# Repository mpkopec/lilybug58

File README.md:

# lilybug58

**Work in progress.** lilybug58 is a split keyboard derived from
[Bug54](https://github.com/ogruendel/bug54-zmk-config) by ogruendel, and this
repository is a fork of the Bug54 repository. It keeps Bug54's
compact, column-staggered layout and adds two keys per half taken from
[Lily58](https://github.com/kata0510/Lily58), for 58 keys in total:

- an index-finger key beside the innermost column, centred between its two
  lowest keys, in the position of the Lily58 extra key;
- a fifth key below the ring-finger column, where a Super key typically sits.

## Status

The design is at an early stage, and nothing in this repository has been
manufactured or tested yet. The PCB is being redesigned in KiCad, starting
from Bug54's ergogen-generated boards, and the firmware moves from ZMK to
QMK.

## Design

- **PCB:** KiCad 10, one project per half in `kicad/`.
- **Microcontroller:** Adafruit Feather RP2040 in the first revision. A later
  revision is planned to stack footprints for several controller boards, so
  that builders can use the board they already own.
- **Firmware:** QMK.
- **Layout sandbox:** ergogen, in `ergogen/`, used to try key positions and
  outlines. `npm install && npm run generate` writes its output to
  `ergogen/output/`; the KiCad projects remain the master copy of the PCB.
- **Case:** `mech/Case.FCStd` is Bug54's FreeCAD case, kept as the starting
  point for the lilybug58 case.

## Credits and license

Based on Bug54 by ogruendel, with key positions taken from Lily58 by
kata0510. Licensed under CC BY 4.0, as inherited from Bug54; see `LICENSE`.

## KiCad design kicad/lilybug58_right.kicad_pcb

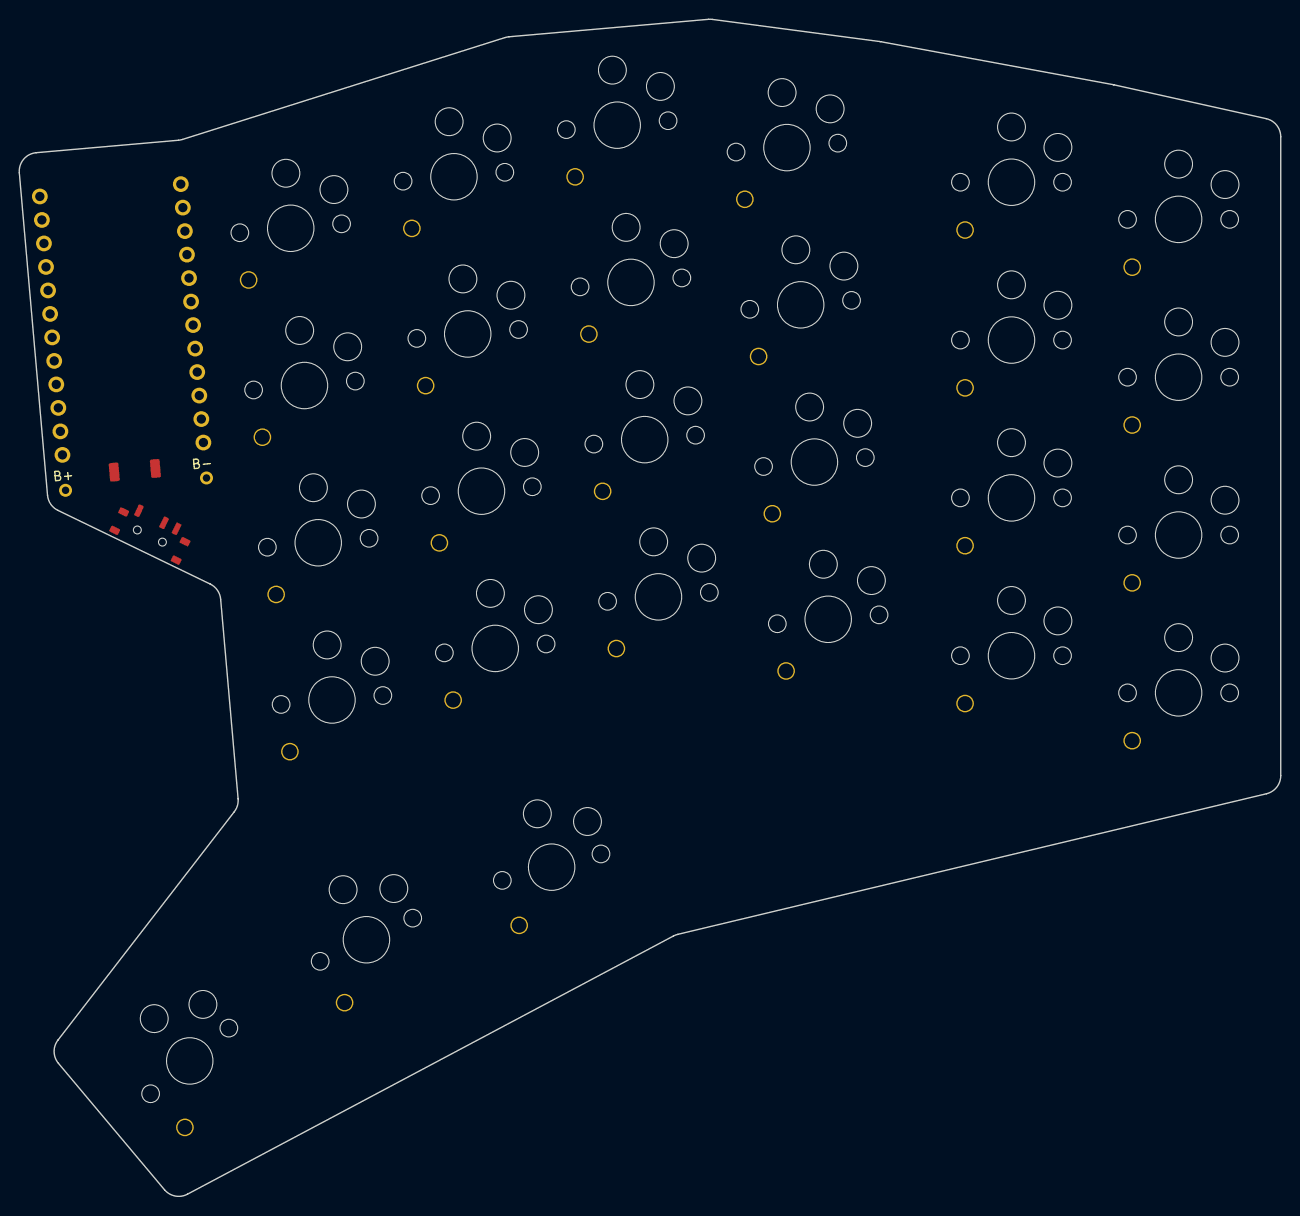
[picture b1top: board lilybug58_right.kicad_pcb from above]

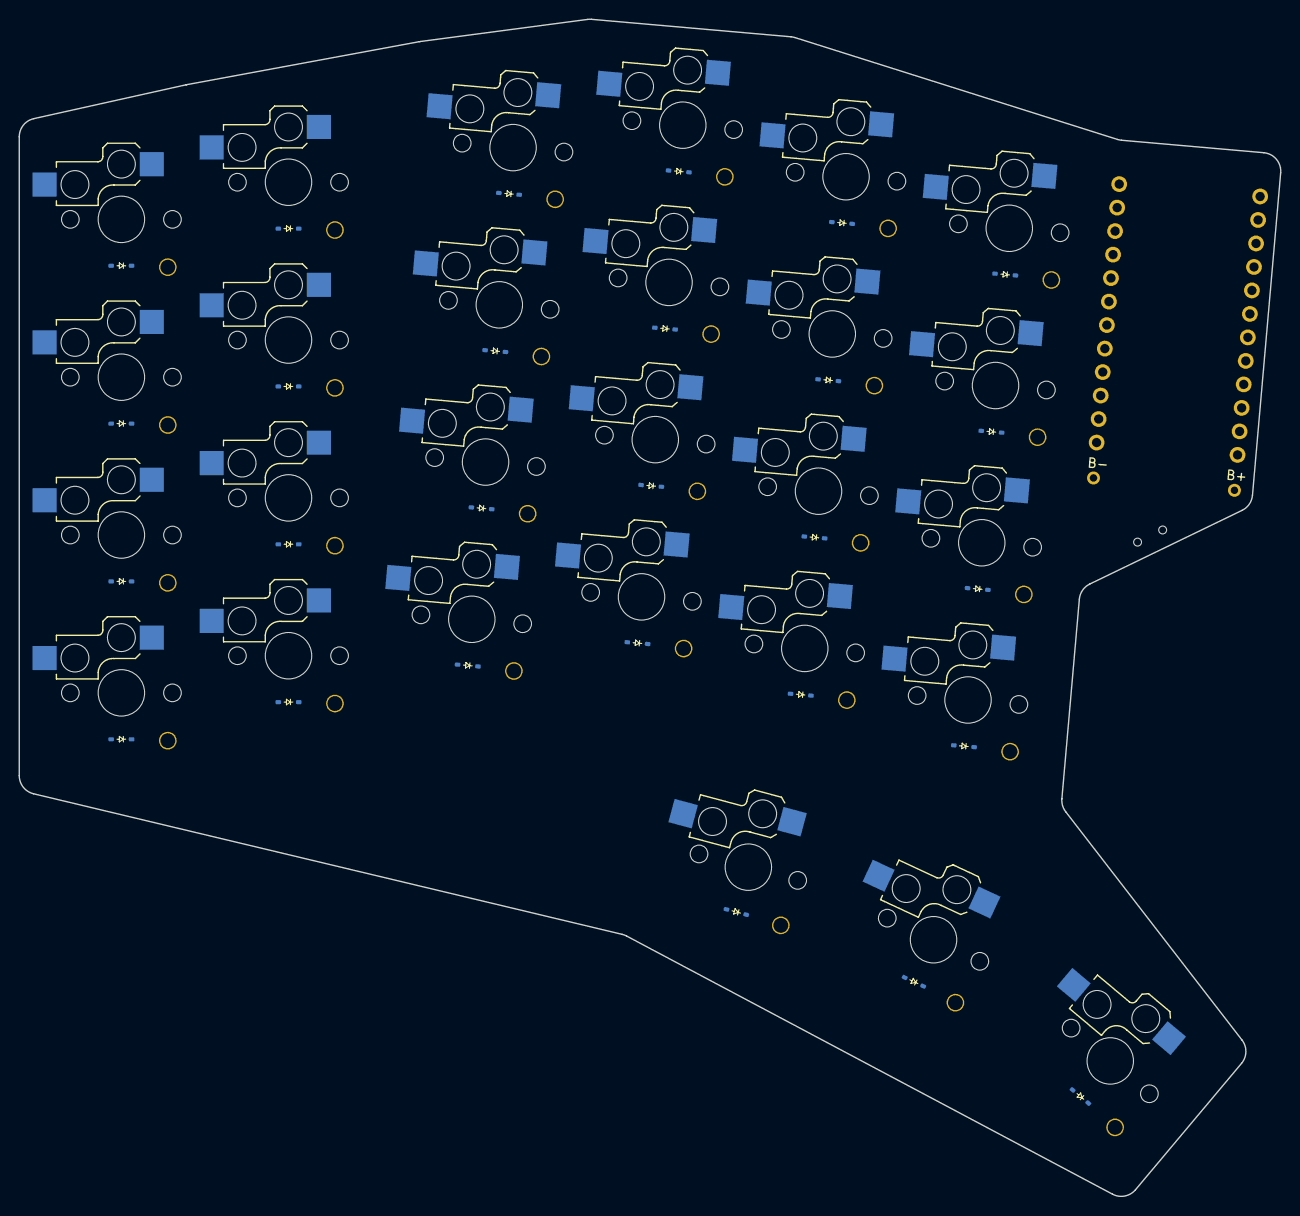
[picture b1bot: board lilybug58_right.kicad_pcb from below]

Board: 2 copper layers, 135.9 x 126.8 mm, 27 parts (27 on the bottom side), 6 nets, no tracks yet.

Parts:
S1, S2, S3, S4, S5, S6, S7, S8, S9, S10, S11, S12, S13, S14, S15, S16, S17, S18, S19, S20, S21, S22, S23, S24, S25, S26, S27: switch_choc_v1_v2

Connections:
P14: S17.1, S18.1, S19.1, S20.1, S26.1
P15: S13.1, S14.1, S15.1, S16.1, S25.1
P16: S21.1, S22.1, S23.1, S24.1, S27.1
P18: S9.1, S10.1, S11.1, S12.1
P19: S5.1, S6.1, S7.1, S8.1
P20: S1.1, S2.1, S3.1, S4.1
